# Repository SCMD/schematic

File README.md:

## SCMD-2 PCB

SCMD-2 design source, schematic and PCB layout.

PDF exports of the schematics, layout and BOM are located in [export](/export)
directory. Deisgn files are located in the root directiry of the repo. To
access the design files you need KiCAD installed.

Make sure that PCU meets EN60601-1 and EN55011 Class B (approved for medical
use). We use widely available [Cincon TR30RAM180](https://www.cincon.com/productdownload/Datasheet-TR30RAM.pdf).

For firmware used with this project navigate [here](https://github.com/SCMD/firmware).

## License

Copyright (C) 2014, Centre for Decision Research and Experimental Economics
(CeDEx), the University of Nottingham.

This documentation describes Open Hardware and is licensed under the CERN OHL
v. 1.2.  You may redistribute and modify this documentation under the terms of
the CERN OHL v.1.2. (http://ohwr.org/cernohl). This documentation is
distributed WITHOUT ANY EXPRESS OR IMPLIED WARRANTY, INCLUDING OF
MERCHANTABILITY, SATISFACTORY QUALITY AND FITNESS FOR A PARTICULAR PURPOSE.
Please see the CERN OHL v.1.2 for applicable conditions

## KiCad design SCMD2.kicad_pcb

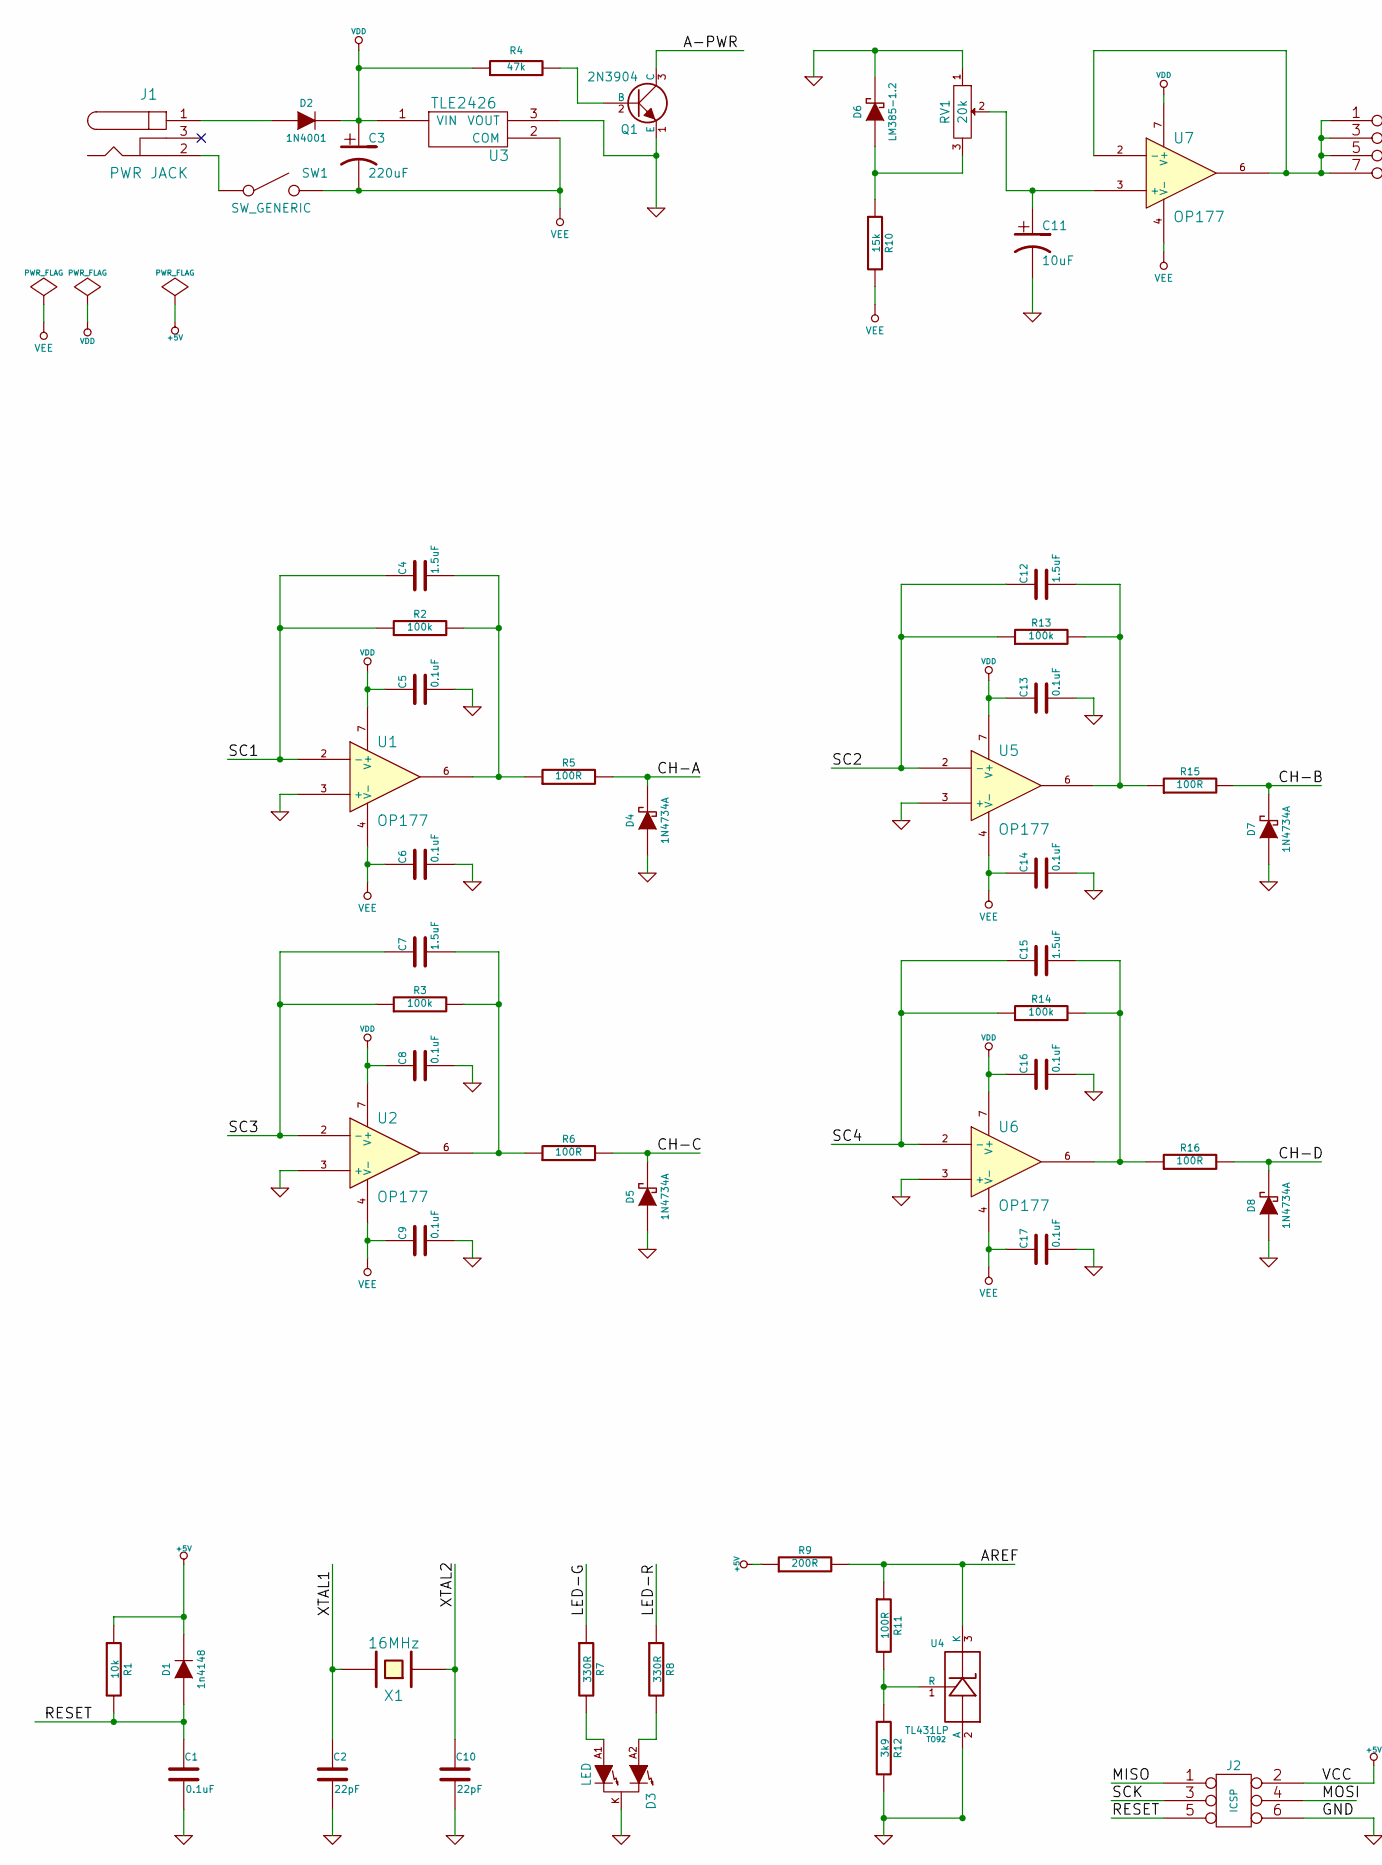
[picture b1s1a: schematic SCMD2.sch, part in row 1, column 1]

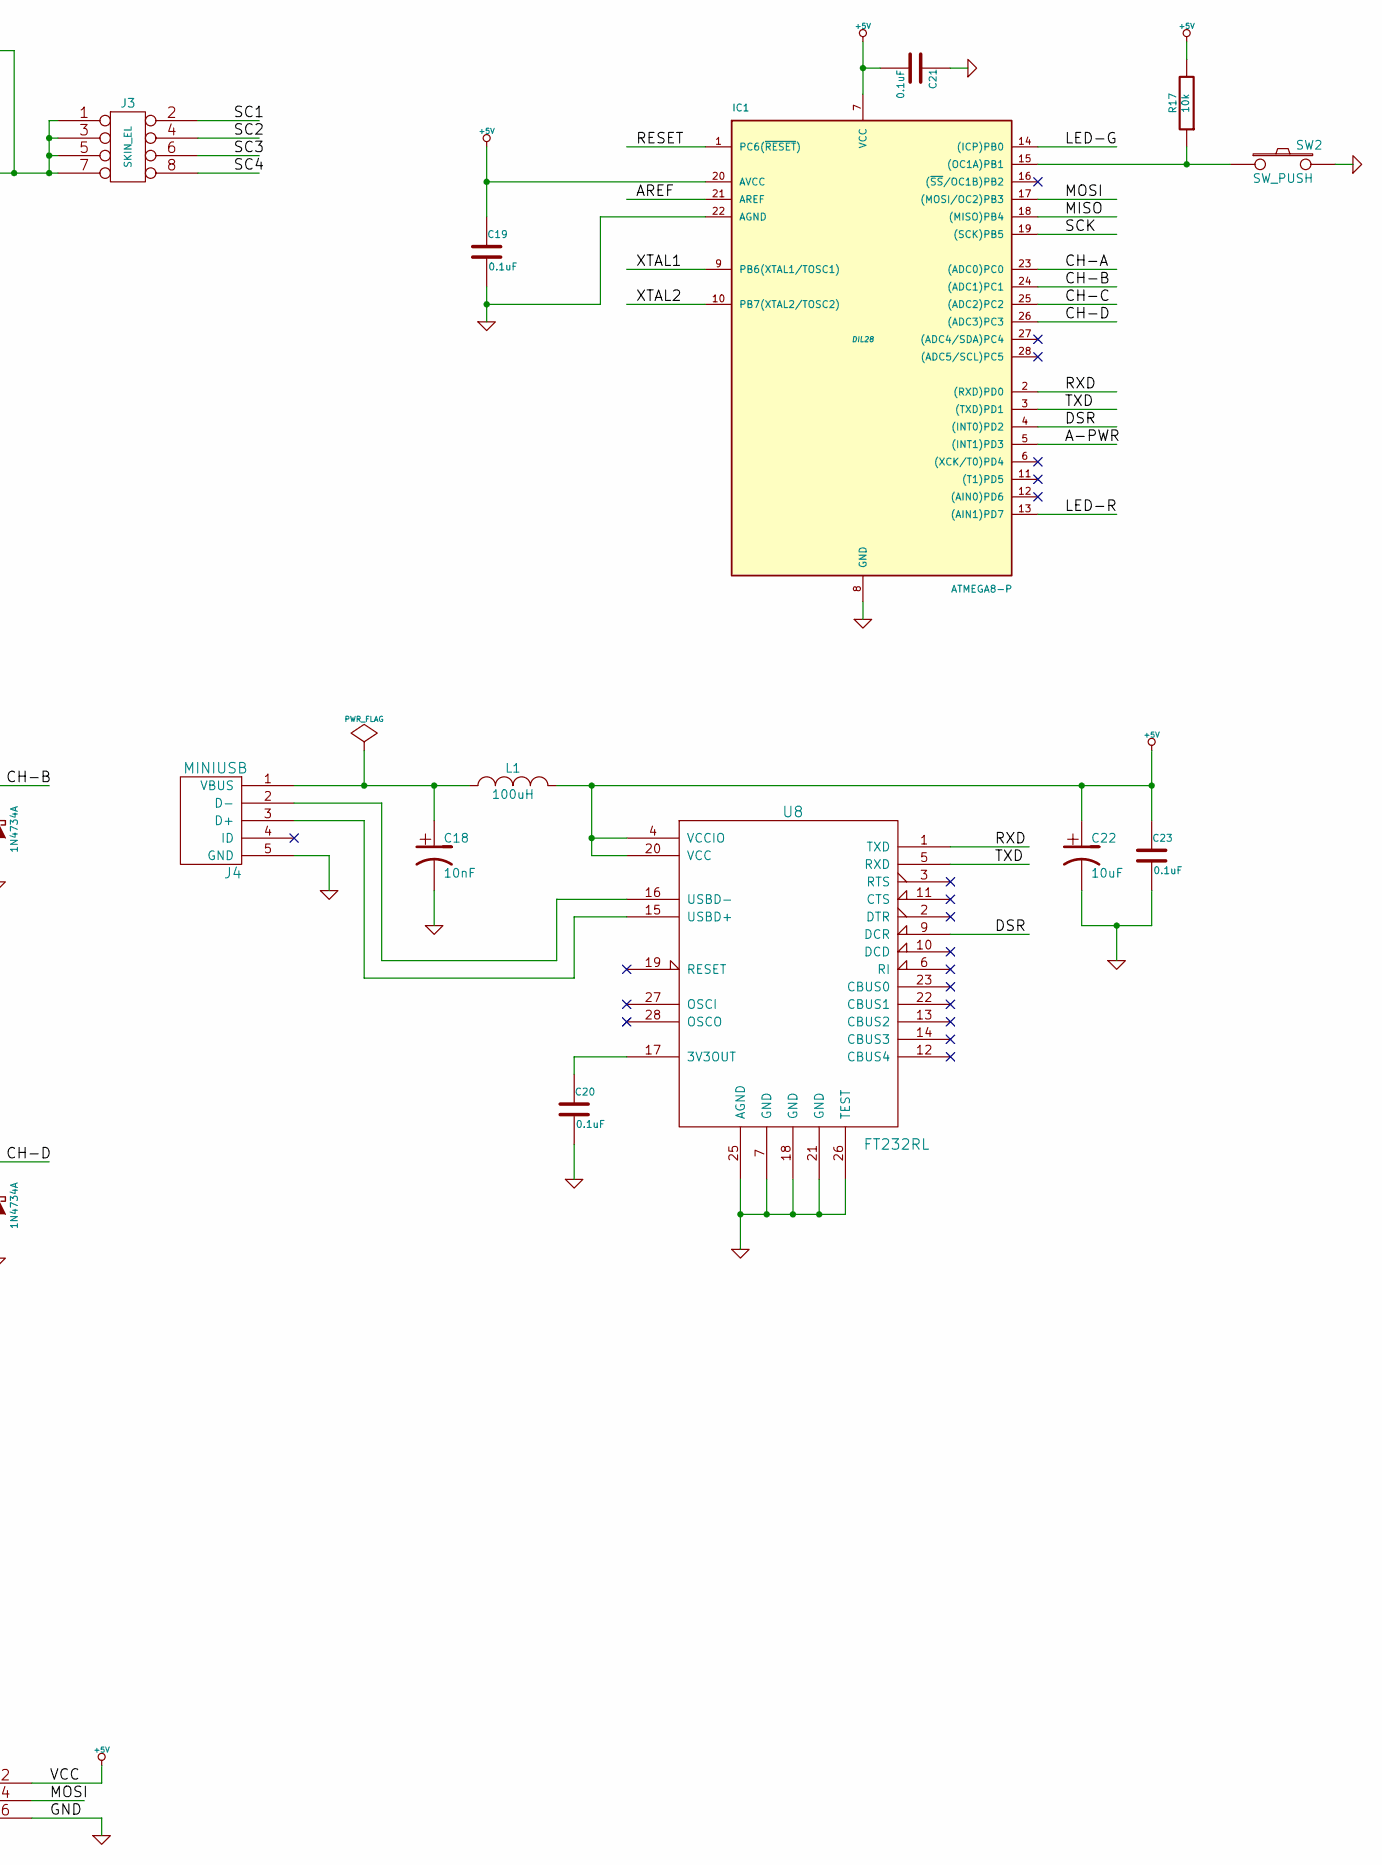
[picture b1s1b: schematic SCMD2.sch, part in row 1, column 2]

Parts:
C1, C5, C6, C8, C9, C13, C14, C16, C17, C19, C20, C21, C23: 0.1uF
C2, C10: 22pF
C3: 220uF
C4, C7, C12, C15: 1.5uF
C11, C22: 10uF
C18: 10nF
D1: 1n4148
D2: 1N4001
D3: LED
D4, D5, D7, D8: 1N4734A
D6: LM385-1.2
IC1: ATMEGA8-P; DIL28
J1: PWR JACK
J2: ICSP
J3: SKIN_EL
J4: MINIUSB
L1: 100uH
Q1: 2N3904
R1, R17: 10k
R2, R3, R13, R14: 100k
R4: 47k
R5, R6, R11, R15, R16: 100R
R7, R8: 330R
R9: 200R
R10: 15k
R12: 3k9
RV1: 20k
SW1: SW_GENERIC
SW2: SW_PUSH
U1, U2, U5, U6, U7: OP177
U3: TLE2426
U4: TL431LP; TO92
U8: FT232RL
X1: 16MHz

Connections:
+5V: C19.1, C21.2, C22.1, C23.1, D1.2 (K), IC1.7 (VCC), IC1.20 (AVCC), J2.2, L1.2, R1.1, R9.1, R17.2, U8.4 (VCCIO), U8.20 (VCC)
/A-PWR: IC1.5 ((INT1)PD3), Q1.3 (C)
/AREF: IC1.21 (AREF), R9.2, R11.1, U4.3 (K)
/CH-A: D4.2 (K), IC1.23 ((ADC0)PC0), R5.2
/CH-B: D7.2 (K), IC1.24 ((ADC1)PC1), R15.2
/CH-C: D5.2 (K), IC1.25 ((ADC2)PC2), R6.2
/CH-D: D8.2 (K), IC1.26 ((ADC3)PC3), R16.2
/DSR: IC1.4 ((INT0)PD2), U8.9 (DCR)
/LED-G: IC1.14 ((ICP)PB0), R7.1
/LED-R: IC1.13 ((AIN1)PD7), R8.1
/MISO: IC1.18 ((MISO)PB4), J2.1
/MOSI: IC1.17 ((MOSI/OC2)PB3), J2.4
/RESET: C1.1, D1.1 (A), IC1.1 (PC6(~RESET~)), J2.5, R1.2
/RXD: IC1.2 ((RXD)PD0), U8.1 (TXD)
/SC1: C4.1, J3.2, R2.1, U1.2 (-)
/SC2: C12.1, J3.4, R13.1, U5.2 (-)
/SC3: C7.1, J3.6, R3.1, U2.2 (-)
/SC4: C15.1, J3.8, R14.1, U6.2 (-)
/SCK: IC1.19 ((SCK)PB5), J2.3
/TXD: IC1.3 ((TXD)PD1), U8.5 (RXD)
/XTAL1: C2.1, IC1.9 (PB6(XTAL1/TOSC1)), X1.2
/XTAL2: C10.1, IC1.10 (PB7(XTAL2/TOSC2)), X1.1
GND: C1.2, C2.2, C5.2, C6.2, C8.2, C9.2, C10.2, C11.2, C13.2, C14.2, C16.2, C17.2, C18.2, C19.2, C20.2, C21.1, C22.2, C23.2, D3.K, D4.1 (A), D5.1 (A), D6.2 (K), D7.1 (A), D8.1 (A), IC1.8 (GND), IC1.22 (AGND), J2.6, J4.5 (GND), Q1.1 (E), R12.2, RV1.1, SW2.2, U1.3 (+), U2.3 (+), U3.3 (VOUT), U4.2 (A), U5.3 (+), U6.3 (+), U8.7 (GND), U8.18 (GND), U8.21 (GND), U8.25 (AGND), U8.26 (TEST)
unnamed: C12.2, R13.2, R15.1, U5.6
unnamed: C15.2, R14.2, R16.1, U6.6
unnamed: C4.2, R2.2, R5.1, U1.6
unnamed: C20.1, U8.17 (3V3OUT)
unnamed: J1.2, SW1.1
unnamed: C18.1, J4.1 (VBUS), L1.1
unnamed: J4.2 (D-), U8.16 (USBD-)
unnamed: J4.3 (D+), U8.15 (USBD+)
unnamed: R11.2, R12.1, U4.1 (R)
unnamed: D3.A1, R7.2
unnamed: D3.A2, R8.2
unnamed: D2.1 (A), J1.1
unnamed: IC1.15 ((OC1A)PB1), R17.1, SW2.1
unnamed: J3.1, J3.3, J3.5, J3.7, U7.2 (-), U7.6
unnamed: C7.2, R3.2, R6.1, U2.6
unnamed: C11.1, RV1.2, U7.3 (+)
unnamed: D6.1 (A), R10.1, RV1.3
unnamed: Q1.2 (B), R4.2
VDD: C3.1, C5.1, C8.1, C13.1, C16.1, D2.2 (K), R4.1, U1.7 (V+), U2.7 (V+), U3.1 (VIN), U5.7 (V+), U6.7 (V+), U7.7 (V+)
VEE: C3.2, C6.1, C9.1, C14.1, C17.1, R10.2, SW1.2, U1.4 (V-), U2.4 (V-), U3.2 (COM), U5.4 (V-), U6.4 (V-), U7.4 (V-)

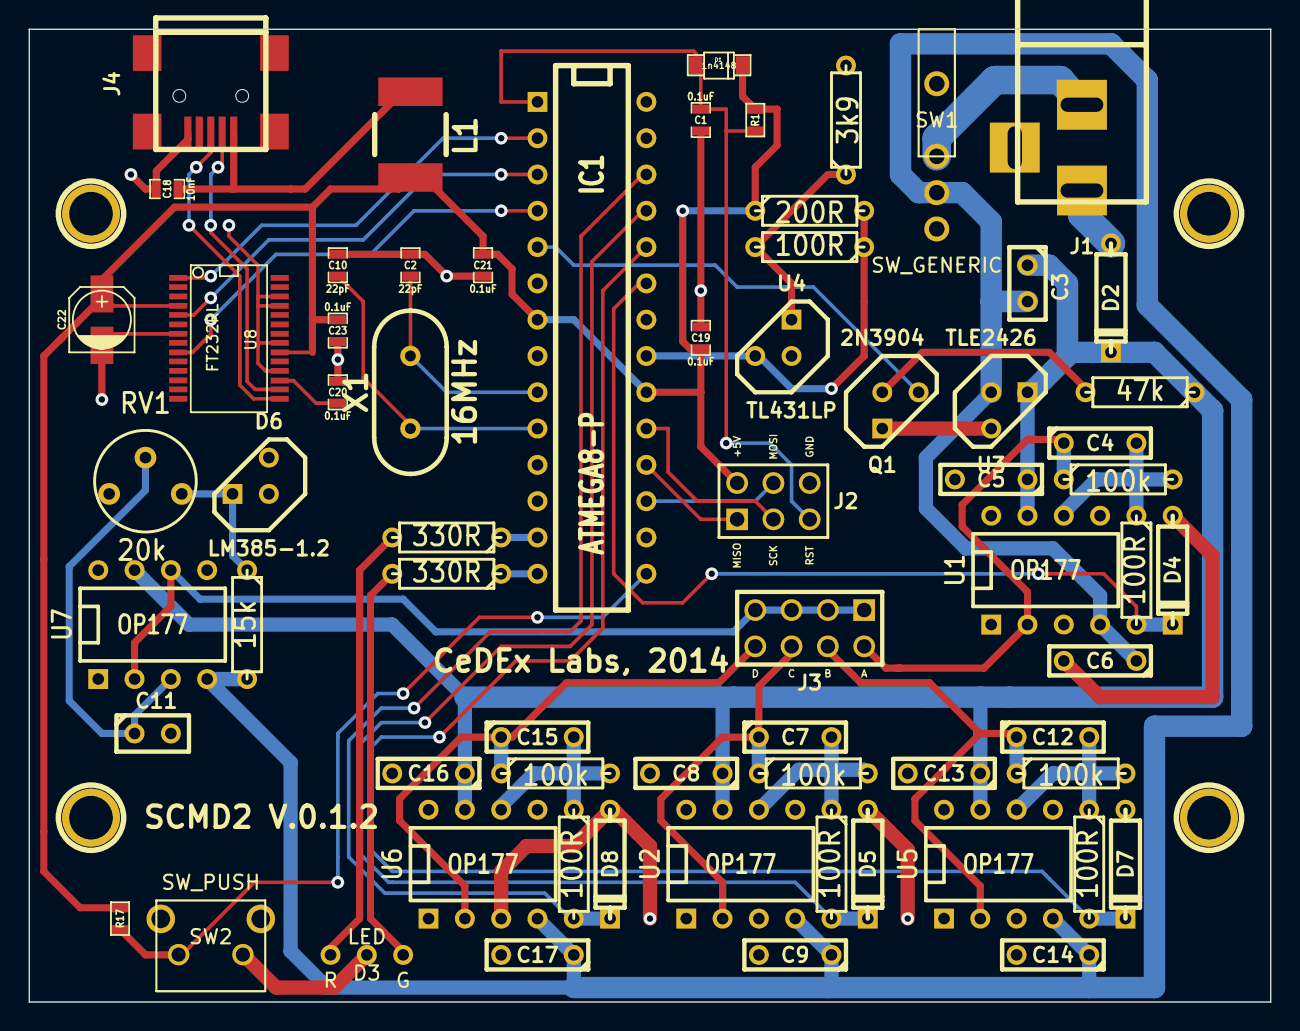
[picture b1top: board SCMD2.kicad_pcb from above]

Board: 2 copper layers, 86.9 x 68.1 mm, 71 parts (0 on the bottom side), 43 nets.

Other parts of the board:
1PIN, 1PIN#2, 1PIN#3, 1PIN#4: P***; 1pin

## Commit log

2014-10-16 Initial commit.
2014-10-16 Add missing mods.
2014-10-16 Add filling zone and connect GND.
2014-10-22 Add board info.
2014-10-24 Fix mini-usb mod and improve ground filling connectivity.
2014-12-02 Remove obsolete mods.
2014-12-02 Refactor PCB and release SCMD2 V.0.1.2
    * Fix L1 footprint,
    * Refactor tracks to avoid their accidential damage,
    * Replace TO92 footprints to match case type,
    * Use SM0603 for R1,
    * Add pin labels for J2 and J3,
    * Add D3 LED labels,
2016-10-05 Add readme, exported files and license.
